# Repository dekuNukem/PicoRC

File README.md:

# PicoRC: PicoPSU on Retro Computers!

[Purchase Link](https://www.tindie.com/stores/dekunukem/items/) | [Official Discord](https://discord.gg/HAuuh3pAmB)

----

PicoRC is a line of replacement **Power-supply Units (PSU)** for vintage computers.

## Features

* **Non-destructive** and **reversible**
* Universal voltage with **fused** rails
* **PC Fan header** for added cooling

For more **general-purpose** diagnostics and retrofitting, check out [ATX4VC](https://dekunukem.github.io/ATX4VC/).

## Available For:

### IBM PC Compatible

[Purchase Link](https://www.tindie.com/products/31437) | [Instructions](ibmpc.md)

### IBM Portable Personal Computer 5155

[Purchase Link](https://www.tindie.com/products/31437) | [Instructions](ibm5155.md)

### Apple II / II Plus / IIe

[Purchase Link](https://www.tindie.com/products/29185/) | [Instructions](appleii.md)

### Apple IIGS

[Purchase Link](https://www.tindie.com/products/30055/) | [Instructions](apple_iigs.md)

### Macintosh 128K / 512K / Plus

[Purchase Link](https://www.tindie.com/products/28754/) | [Instructions](og_mac.md)

### Macintosh SE & SE/30

[Purchase Link](https://www.tindie.com/products/29184/) | [Instructions](mac_se_se30.md)

### BBC Micro

[Purchase Link](https://www.tindie.com/products/31079/) | [Instructions](bbc_micro.md)

### BBC Master

[Purchase Link](https://www.tindie.com/products/31079/) | [Instructions](bbc_master.md)

### ACT Sirius 1 / Victor 9000

[Purchase Link](https://www.tindie.com/products/41802/) | [Instructions](sirius1.md)

### Apricot PC / PC XI / PC286

[Purchase Link](https://www.tindie.com/products/31080/) | [Instructions](apricot_pc.md)

### Osborne 1

[Purchase Link](https://www.tindie.com/products/30087/) | [Instructions](osborne1.md)

## Get in Touch

Join our official [Discord Chatroom](https://discord.gg/T9uuFudg7j) for updates.

Questions or comments? Ask in Discord, or raise a [Github issue](https://github.com/dekuNukem/ATX4VC/issues), or email `dekunukem` `gmail.com`!

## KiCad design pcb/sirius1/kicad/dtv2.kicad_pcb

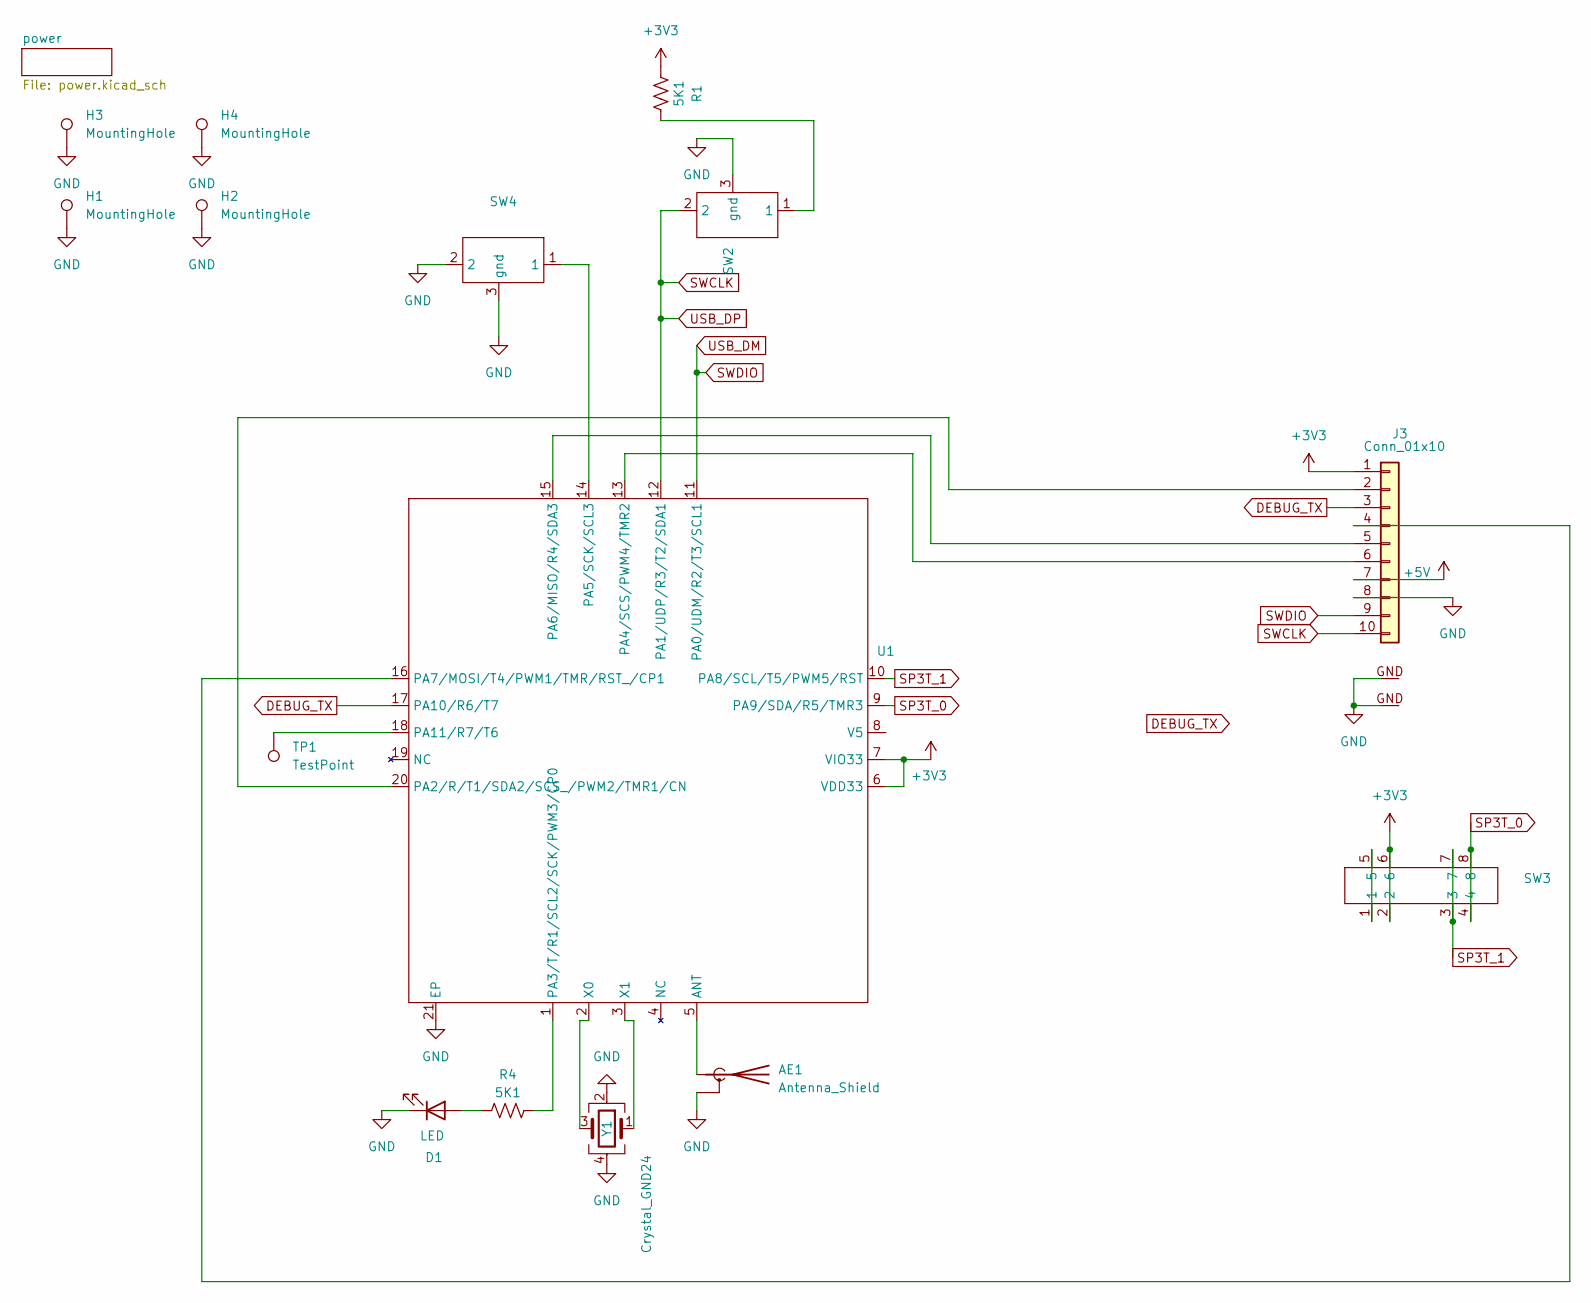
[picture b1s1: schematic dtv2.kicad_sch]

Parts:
AE1: Antenna_Shield; ESPRESSIF_ESP32_MIFA_2.4GHz_Right
D1: LED; LED_0805_2012Metric
H1, H2, H3, H4: MountingHole; MountingHole_2.2mm_M2_ISO7380_Pad
J3: Conn_01x10; JST_SH_BM10B-SRSS-TB_1x10-1MP_P1.00mm_Vertical
R1, R4: 5K1; R_0805_2012Metric
SW2, SW4: turt
SW3: my_sp3t_pth
TP1: TestPoint; TestPoint_Plated_Hole_D2.0mm
U1: QFN-20-1EP_3x3mm_P0.4mm_EP1.65x1.65mm
Y1: Crystal_GND24; Crystal_SMD_3225-4Pin_3.2x2.5mm

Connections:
+3V3: J3.1, R1.1, SW3.2, SW3.6, U1.6 (VDD33), U1.7 (VIO33); also elsewhere on the board
+5V: J3.7; also elsewhere on the board
DEBUG_TX: J3.3, U1.17 (PA10/R6/T7)
GND: AE1.2 (Shield), D1.1 (K), H1.1, H2.1, H3.1, H4.1, J3.8, J3.GND, SW2.3 (gnd), SW4.2, SW4.3 (gnd), U1.21 (EP), Y1.2, Y1.4; also elsewhere on the board
unnamed: AE1.1 (A), U1.5 (ANT)
unnamed: D1.2 (A), R4.1
unnamed: J3.2, U1.20 (PA2/R/T1/SDA2/SCS_/PWM2/TMR1/CN)
unnamed: J3.4, U1.16 (PA7/MOSI/T4/PWM1/TMR/RST_/CP1)
unnamed: J3.5, U1.15 (PA6/MISO/R4/SDA3)
unnamed: J3.6, U1.13 (PA4/SCS/PWM4/TMR2)
unnamed: R1.2, SW2.1
unnamed: SW3.1, SW3.5
unnamed: R4.2, U1.1 (PA3/T/R1/SCL2/SCK/PWM3/CP0)
unnamed: SW4.1, U1.14 (PA5/SCK/SCL3)
unnamed: TP1.1, U1.18 (PA11/R7/T6)
unnamed: U1.2 (X0), Y1.3
unnamed: U1.3 (X1), Y1.1
SP3T_0: SW3.4, SW3.8, U1.9 (PA9/SDA/R5/TMR3)
SP3T_1: SW3.3, SW3.7, U1.10 (PA8/SCL/T5/PWM5/RST)
SWCLK: J3.10, SW2.2, U1.12 (PA1/UDP/R3/T2/SDA1); also elsewhere on the board
SWDIO: J3.9, U1.11 (PA0/UDM/R2/T3/SCL1); also elsewhere on the board

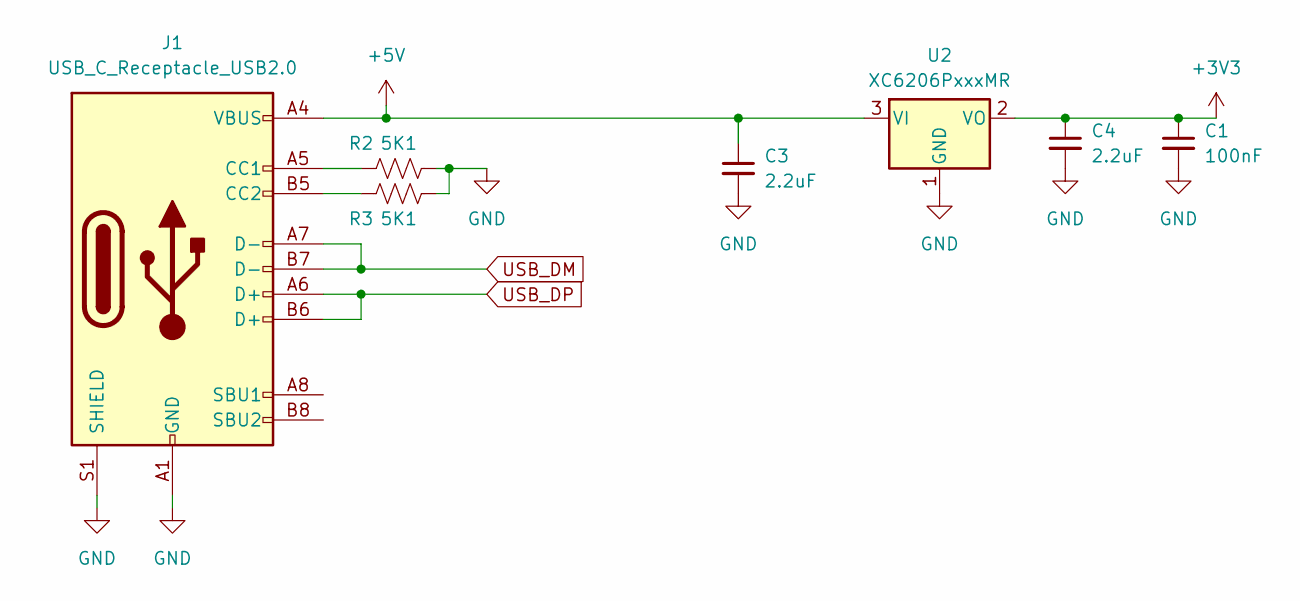
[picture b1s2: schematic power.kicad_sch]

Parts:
C1: 100nF; C_0805_2012Metric
C3, C4: 2.2uF; C_0805_2012Metric
J1: USB_C_Receptacle_USB2.0; USB_C_Receptacle_HRO_TYPE-C-31-M-12
R2, R3: 5K1; R_0805_2012Metric
U2: XC6206PxxxMR; SOT-23-3

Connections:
+3V3: C1.1, C4.1, U2.2 (VO); also elsewhere on the board
+5V: C3.1, J1.A4 (VBUS), J1.A9 (VBUS), J1.B4 (VBUS), J1.B9 (VBUS), U2.3 (VI); also elsewhere on the board
GND: C1.2, C3.2, C4.2, J1.A1 (GND), J1.A12 (GND), J1.B1 (GND), J1.B12 (GND), J1.S1 (SHIELD), R2.2, R3.2, U2.1 (GND); also elsewhere on the board
unnamed: J1.A5 (CC1), R2.1
unnamed: J1.B5 (CC2), R3.1
SWCLK: J1.A6 (D+), J1.B6 (D+); also elsewhere on the board
SWDIO: J1.A7 (D-), J1.B7 (D-); also elsewhere on the board

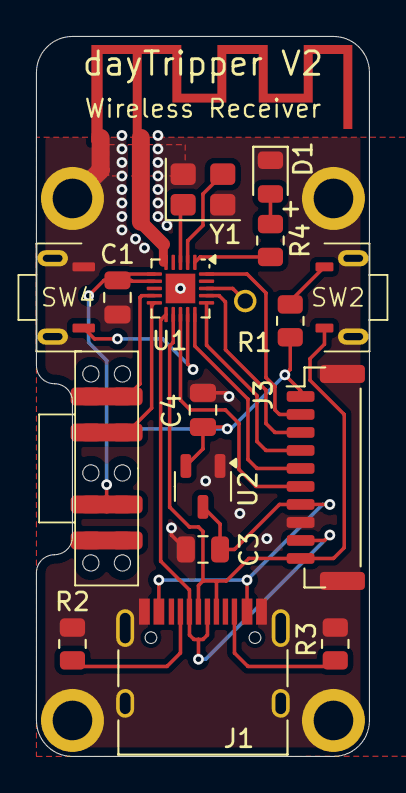
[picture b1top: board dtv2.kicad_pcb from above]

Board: 2 copper layers, 18.5 x 40.0 mm, 22 parts (0 on the bottom side), 23 nets.

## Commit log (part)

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2022-12-12 moved files from ATX4VC to here
2022-12-12 writing doc
2022-12-12 updated silkscreen
2022-12-13 updated switch location
2022-12-16 updated pcb
2022-12-19 added iigs power header
2022-12-20 added iigs
2023-01-25 added macse
2023-01-25 added apple ii
2023-01-25 cleanup
2023-01-25 updated links
2023-01-25 fixed typo
2023-02-08 added instruction about nylon rivets
2023-03-09 added BBC micro
2023-03-09 added one more -5v rail
2023-03-09 finishing touches
2023-03-27 BBC micro USB adaptor
2023-04-03 added osborne 1
2023-04-05 working on edgeplate
2023-04-08 updated IIGS design
2023-04-08 updated silkscreen and improved GND return
2023-04-08 updated bbc micro PCB
2023-04-09 cleaned up photo link
2023-04-09 changed bbc micro PCB with LM2776
2023-04-09 clean up for production run
2023-04-10 fixed header photo
2023-04-11 fixed a silkscreen error
2023-04-14 added one more power connector, added decoupling cap
2023-04-15 changed oritation
2023-04-15 correct orientation to allow grounding blade
2023-04-15 minor cleanup
2023-04-17 adjusted lm2776 footprint
2023-04-18 updated new photos with PCB blanking plate
2023-04-19 writing doc for IIGS
2023-04-20 added money shot
2023-04-20 new photos
2023-04-20 clean up wording
2023-04-20 updated parts
2023-04-21 working on osborne 1
2023-04-21 adjusted switch position
2023-04-21 added more photos
2023-04-21 fixed broken link
2023-04-24 added product link
2023-04-24 added stl files for mac SE plates
2023-06-01 bbc run
2023-06-09 minor
2023-06-10 added apricot pc
2023-06-10 added more caps
2023-06-10 adjusted holes
2023-06-18 added grounding blade and exposed screw pad, added psw blade
2023-06-19 minor adjustment before production
2023-06-19 working on ibmpc
2023-06-19 ibmpc done
2023-06-19 adjust apricot pc resistors
2023-06-20 changed ibm switch position
2023-06-26 fixed connector oritation
2023-06-27 changed to 70L05
2023-06-27 switched back to 7905
2023-06-27 added ISA legs
2023-06-27 LED now shows power good signal
2023-06-30 minor adjustments
2023-07-03 connected up switch, adjusted mounting hole
2023-07-03 changed to small diameter caps
2023-07-03 changed to smaller diameter caps
2023-07-03 added blanking plate
2023-07-04 cleanup for new run
2023-07-05 adding fingers
2023-07-05 added voltage blaster features, removed 3.3V
2023-07-10 added fingers for 5V and 12V, minor adjustments
2023-07-11 added 3V3 load resistor, flipped board around
2023-07-11 moved psw header location
2023-07-13 working on apricot PC
2023-07-14 adjusted opening
2023-07-17 added apricot PC and BBC micro
2023-07-17 updated new version
2023-07-17 updated apple II doc
2023-07-17 added product links
2023-07-21 working on IBM card
2023-07-22 working on new version
2023-07-22 added more caps to OS1
2023-07-24 cleaned up links
2023-07-24 clean up
2023-07-25 updated fan header
2023-07-27 adjusted USB opening and text
2023-07-28 removed fan voltage selector
2023-07-28 working on improvements
2023-07-31 added 12V load resistor and blade
2023-08-01 updated with more caps
2023-08-04 fixed a typo
2023-08-12 updated OS1 guide with new revision
2023-08-12 working on ibm
2023-08-14 adjusted footprint
2023-08-16 writing
2023-08-16 writing about big red switch
2023-08-17 working on 5155
2023-08-17 5155 write
2023-08-17 more photos
2023-08-19 putting 5155 in its own article
2023-08-22 cleaning up
2023-08-22 added more about big red switch
2023-08-22 added ibm money shot
2023-09-07 updated photos
2023-09-07 updated docs
2023-09-24 updated blanking plate
2023-09-24 trace cleanup
2023-11-07 updated 5155 and PC warning
2023-12-28 updated part list
2023-12-28 updated mac128k guide
2024-01-23 adding guide for early osborne 1
2024-01-23 early osborne 1
2024-03-17 added instruction for eariler apple IIs
2024-03-17 enlarged blanking plate for apple II and II plus
2024-04-04 pcb se30 blanking plate
2024-04-27 added isa bracket
2024-10-28 silkscreen adjustment
2024-10-28 using github pages
2025-03-03 updated backplate
2025-03-13 test fit adjustment
2025-03-22 added osborne1 stl files
2025-03-23 added BBC master instructions
2025-05-26 added gerbers
2025-09-18 rev2, added internal usbc port, silkscreen cleanup
2025-09-18 adjusted jumper angle, fixed pin bug
2025-10-15 working on improved os1 design
2025-10-15 added docs
2025-10-15 working on trs80_m2
2025-10-16 trs80m2 done
2025-10-16 new os1 pcb done
2025-10-25 isolated pe and gnd
2025-10-25 reworking trs80m2
2025-11-22 added 3d models and gerber files
2025-12-04 added 3d print
2026-02-19 adjust pcb
2026-02-19 working on os1
2026-02-20 working on sirius 1
2026-02-20 396 sirius1
2026-02-21 working on mw psu footprint
2026-02-21 sirius 1 done
2026-02-21 file cleanup
2026-02-21 adjust inductor hole size
2026-02-21 mw os1
2026-02-21 adjusted thermals
2026-02-21 adjusted silkscreen
2026-03-04 m3 holes, moved PSU down slighly, thicker 12V trace
2026-03-21 new branch
2026-03-21 working on sirius 1 doc
2026-03-22 doc clean
2026-03-22 more writing
2026-03-23 doc close to done
2026-04-01 doc cleanup
2026-04-01 updated purchase links
2026-04-02 update wording
2026-04-03 enlarged m3 hole slightly
2026-04-07 updated instruction
2026-05-09 updated osborne 1 pcb
2026-05-23 update os1 pcb
2026-05-24 mean well osborne 1
2026-05-24 os1 early meanwell
2026-05-24 fix typo
2026-05-25 adjust wording
2026-05-28 adjust trace spacing
